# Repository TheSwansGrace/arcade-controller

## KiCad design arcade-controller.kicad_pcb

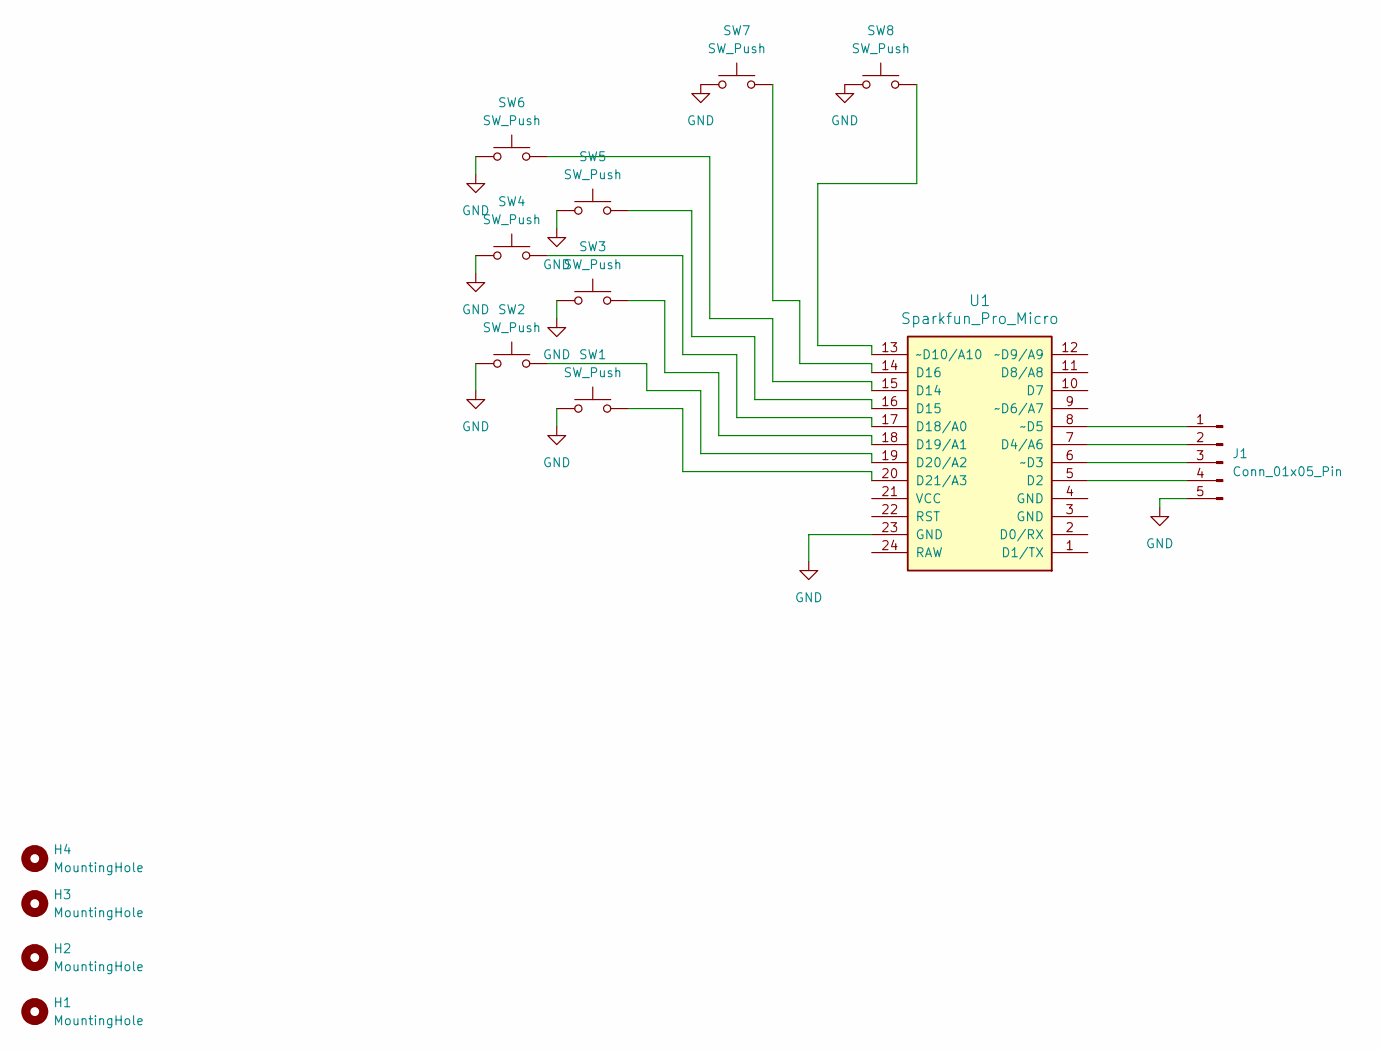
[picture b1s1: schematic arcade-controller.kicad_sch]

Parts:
H1, H2, H3, H4: MountingHole; MountingHole_3.2mm_M3
J1: Conn_01x05_Pin; PinSocket_1x05_P2.54mm_Vertical
SW1, SW2, SW3, SW4, SW5, SW6, SW7, SW8: SW_Push; SW_Cherry_MX_1.00u_PCB
U1: Sparkfun_Pro_Micro

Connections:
GND: J1.5, SW1.1, SW2.1, SW3.1, SW4.1, SW5.1, SW6.1, SW7.1, SW8.1, U1.23 (GND)
unnamed: J1.1, U1.8 (~D5)
unnamed: J1.2, U1.7 (D4/A6)
unnamed: J1.3, U1.6 (~D3)
unnamed: J1.4, U1.5 (D2)
unnamed: SW6.2, U1.15 (D14)
unnamed: SW5.2, U1.16 (D15)
unnamed: SW7.2, U1.14 (D16)
unnamed: SW4.2, U1.17 (D18/A0)
unnamed: SW3.2, U1.18 (D19/A1)
unnamed: SW2.2, U1.19 (D20/A2)
unnamed: SW1.2, U1.20 (D21/A3)
unnamed: SW8.2, U1.13 (~D10/A10)

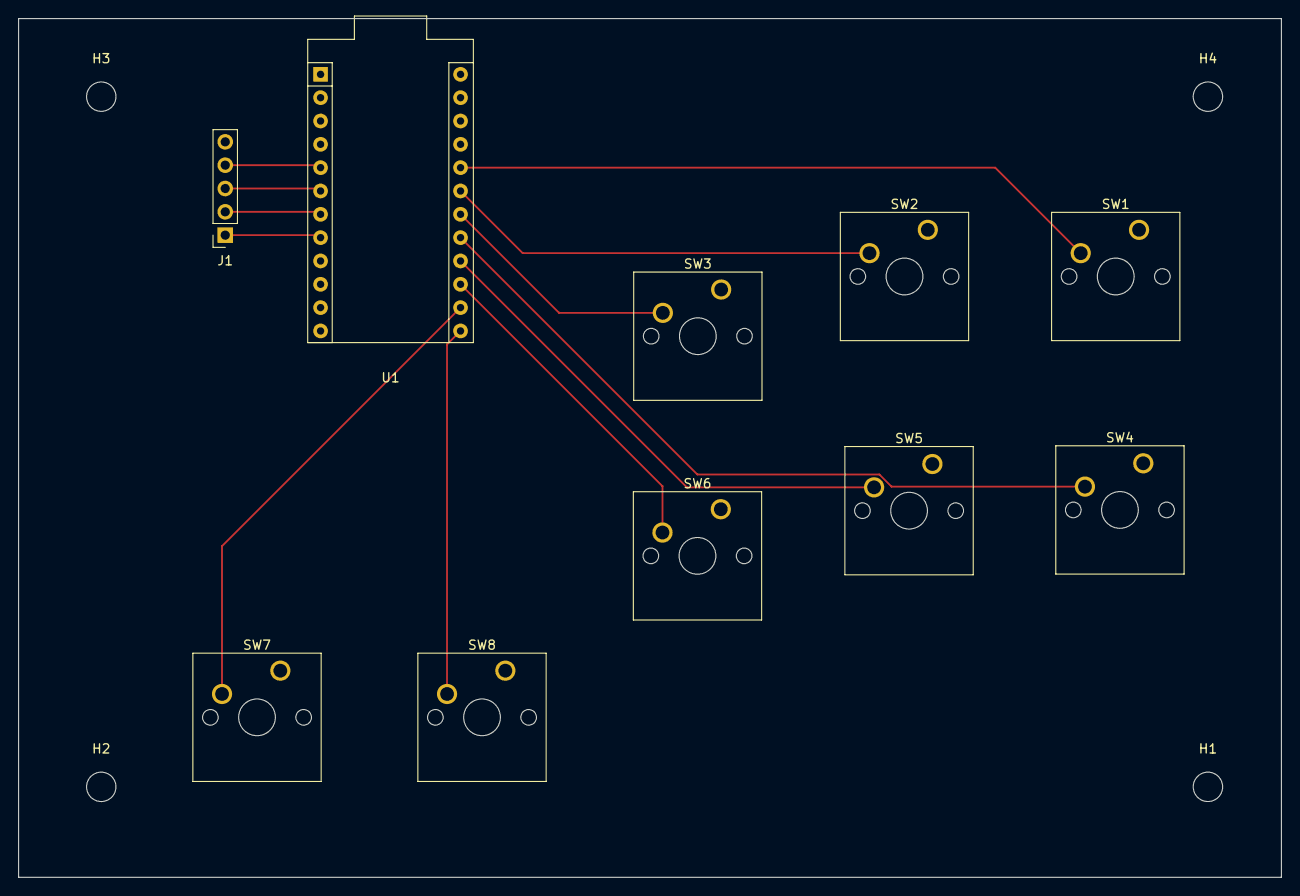
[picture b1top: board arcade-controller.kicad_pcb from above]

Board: 2 copper layers, 137.5 x 93.5 mm, 14 parts (0 on the bottom side), 13 nets.

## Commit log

2025-10-07 Initial Commit, first PCB
2025-10-08 Fixed it with proMicro
2025-10-08 test 1
2025-10-08 undo test
2025-10-09 added mounting holes
2025-10-09 Generated gerber files, submitted for class
